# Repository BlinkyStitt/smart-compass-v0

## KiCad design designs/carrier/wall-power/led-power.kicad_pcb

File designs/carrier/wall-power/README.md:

# Wall-power boards

| Board | KiCad layout | KiCad schematic | Finished board |
| --- | --- | --- | --- |
| Internal charger | [Charger PCB](charger.kicad_pcb) | [Charger schematic](charger.kicad_sch) | 24 × 26 mm, 1.60 mm thick |
| Rev A 5 V external pigtail | [Pigtail PCB](usb-pigtail.kicad_pcb) | [Pigtail schematic](usb-pigtail.kicad_sch) | 28 × 31 mm, **1.20 ± 0.10 mm** thick |
| 60 W USB-C inlet | [Inlet PCB](usb-pd60.kicad_pcb) | [Inlet schematic](usb-pd60.kicad_sch) | 28 × 31 mm, **1.20 ± 0.10 mm** thick |
| LED power selector | [Selector PCB](led-power.kicad_pcb) | [Selector schematic](led-power.kicad_sch) | 28 × 28 mm, 1.60 mm thick |

Build the 60 W inlet, selector and existing charger together. Use the
[60 W BOM](bom-pd60.csv) and [assembly guide](../wall-power-pd60.md).
The 5 V pigtail is the earlier option. The 60 W inlet requires the
programmed STUSB4500 profile. Use the keyed connectors in the assembly
guide to preserve the 5 V and return pin order.

Use KiCad 10. Each board has four copper layers. Specify 35 µm finished
outer copper and at least 35 µm on In2.Cu, which carries the power trunks.
Specify 0.13 mm minimum track, 0.20 mm minimum copper clearance and
0.30 mm copper-to-edge clearance. Use plated slots at the USB receptacle
and nonplated locator and mounting holes. Fill and copper-cap the vias
under the soldered exposed pads, and the other vias placed in SMD pads,
to prevent solder loss. The fabrication drill files do not specify
via fill. Tell the assembler which vias are in pads. The selector uses
0.25 mm finished via drills and a 0.50 mm minimum via diameter.

Use the [charger and 5 V pigtail BOM](bom.csv) for those assemblies.
Reflow the boards and solder the wires at the bench. Fit the USB shell
stakes per the assembly house's mixed SMT and through-hole process.
Check capacitor substitutions at DC bias. The charger needs at least
10 µF effective at BAT and SYS. Use the [assembly and bench guide](../wall-power.md)
for wiring, mounting and commissioning.

## Verify or export the boards

From this directory, with KiCad's footprint libraries installed, run the
following for each name in the table. Use a writable output directory.
Use KiCad's Python interpreter for the scripts that import `pcbnew`.

```sh
board=usb-pd60  # or led-power, charger, usb-pigtail
kicad-cli pcb drc --refill-zones --severity-all --exit-code-violations --schematic-parity \
  -o "$output/$board-drc.rpt" "$board.kicad_pcb"
kicad-cli sch export netlist --format kicadxml \
  -o "$output/$board.xml" "$board.kicad_sch"
python verify_netlist.py "$board.kicad_pcb" "$output/$board.xml"
kicad-cli pcb export gerbers --layers F.Cu,In1.Cu,In2.Cu,B.Cu,F.Paste,F.Silkscreen,B.Silkscreen,F.Mask,B.Mask,Edge.Cuts \
  -o "$output/$board/" "$board.kicad_pcb"
kicad-cli pcb export drill --excellon-separate-th -o "$output/$board/" "$board.kicad_pcb"
kicad-cli pcb export pos --format csv --units mm --smd-only \
  -o "$output/$board/placement.csv" "$board.kicad_pcb"
```

The committed PCB files own the final routes. [Board source](board_design.py)
generates the footprints, pin maps and fixed power copper for a new route.
[Schematic source](schematic.py) generates the KiCad connection drawings
from those pin maps. The netlist comparison checks each footprint, reference
and connected pad. The first assembled pair still needs the bench checks.

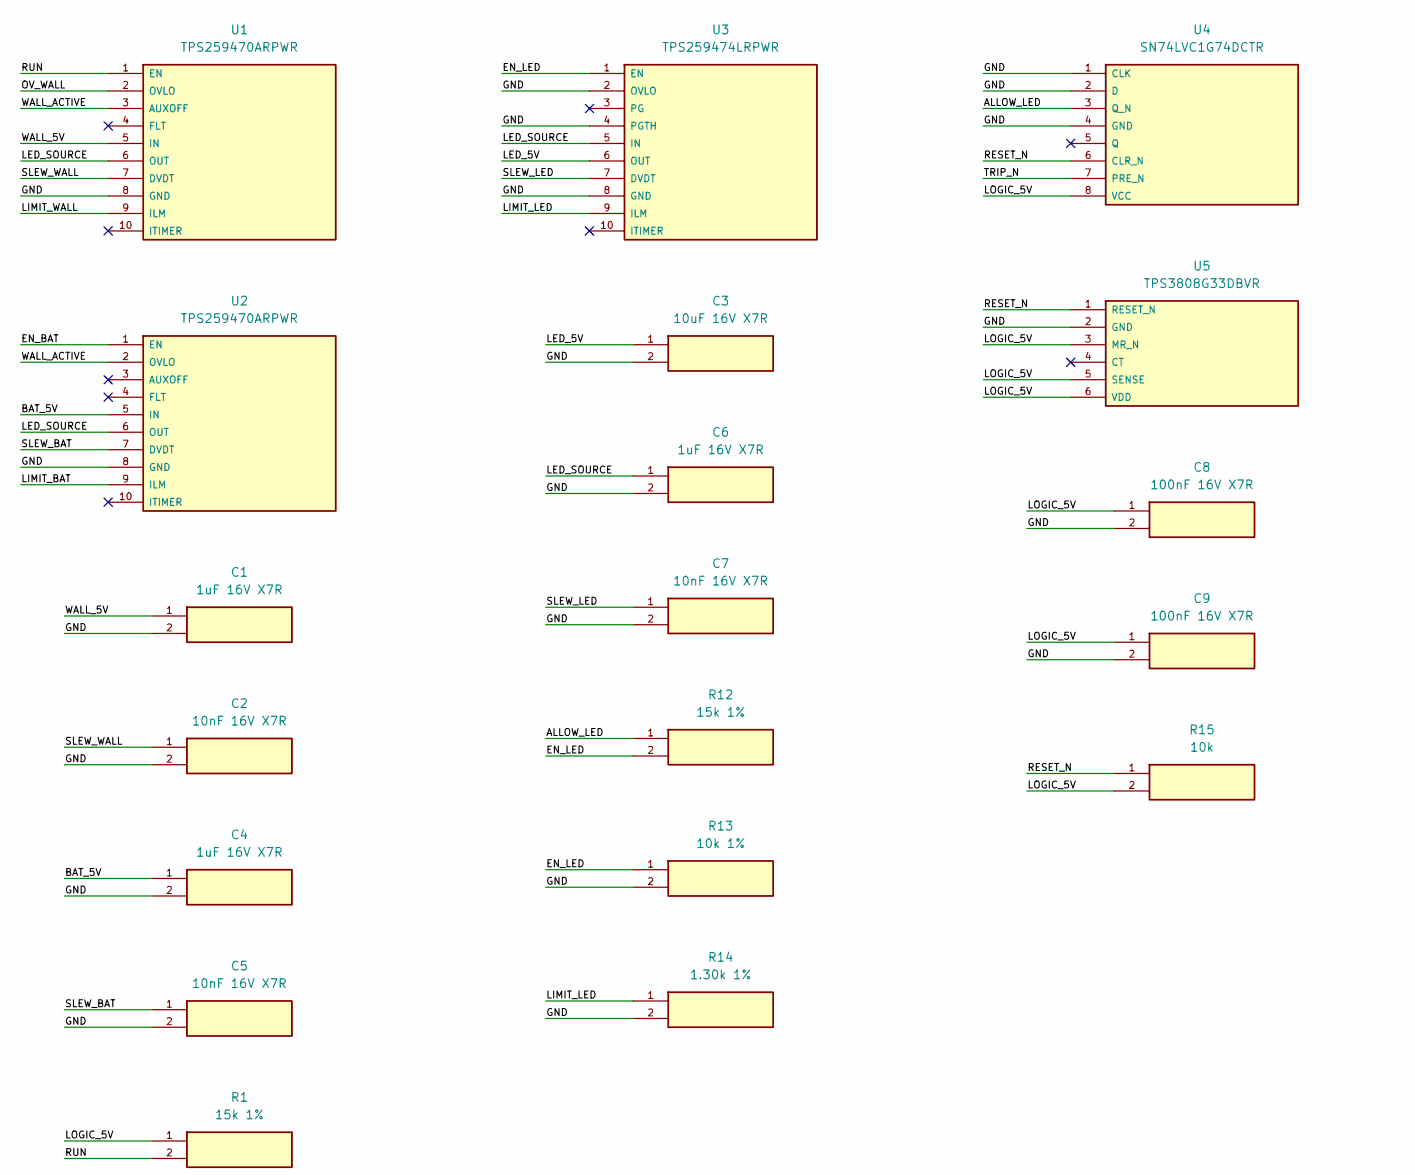
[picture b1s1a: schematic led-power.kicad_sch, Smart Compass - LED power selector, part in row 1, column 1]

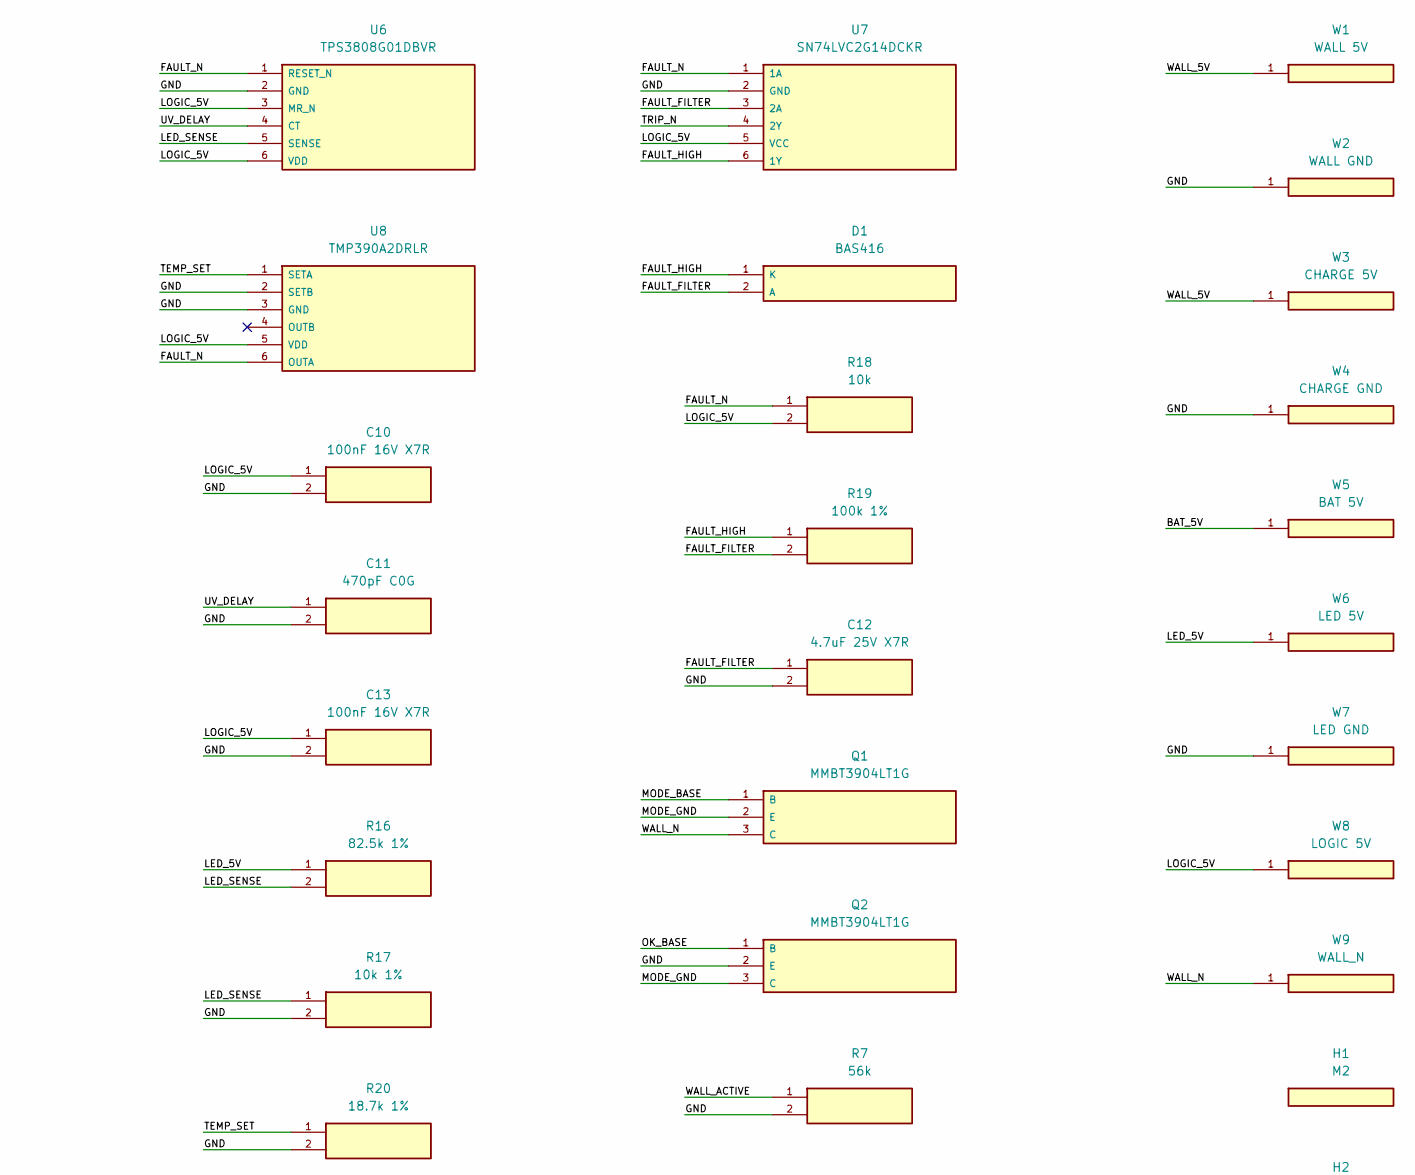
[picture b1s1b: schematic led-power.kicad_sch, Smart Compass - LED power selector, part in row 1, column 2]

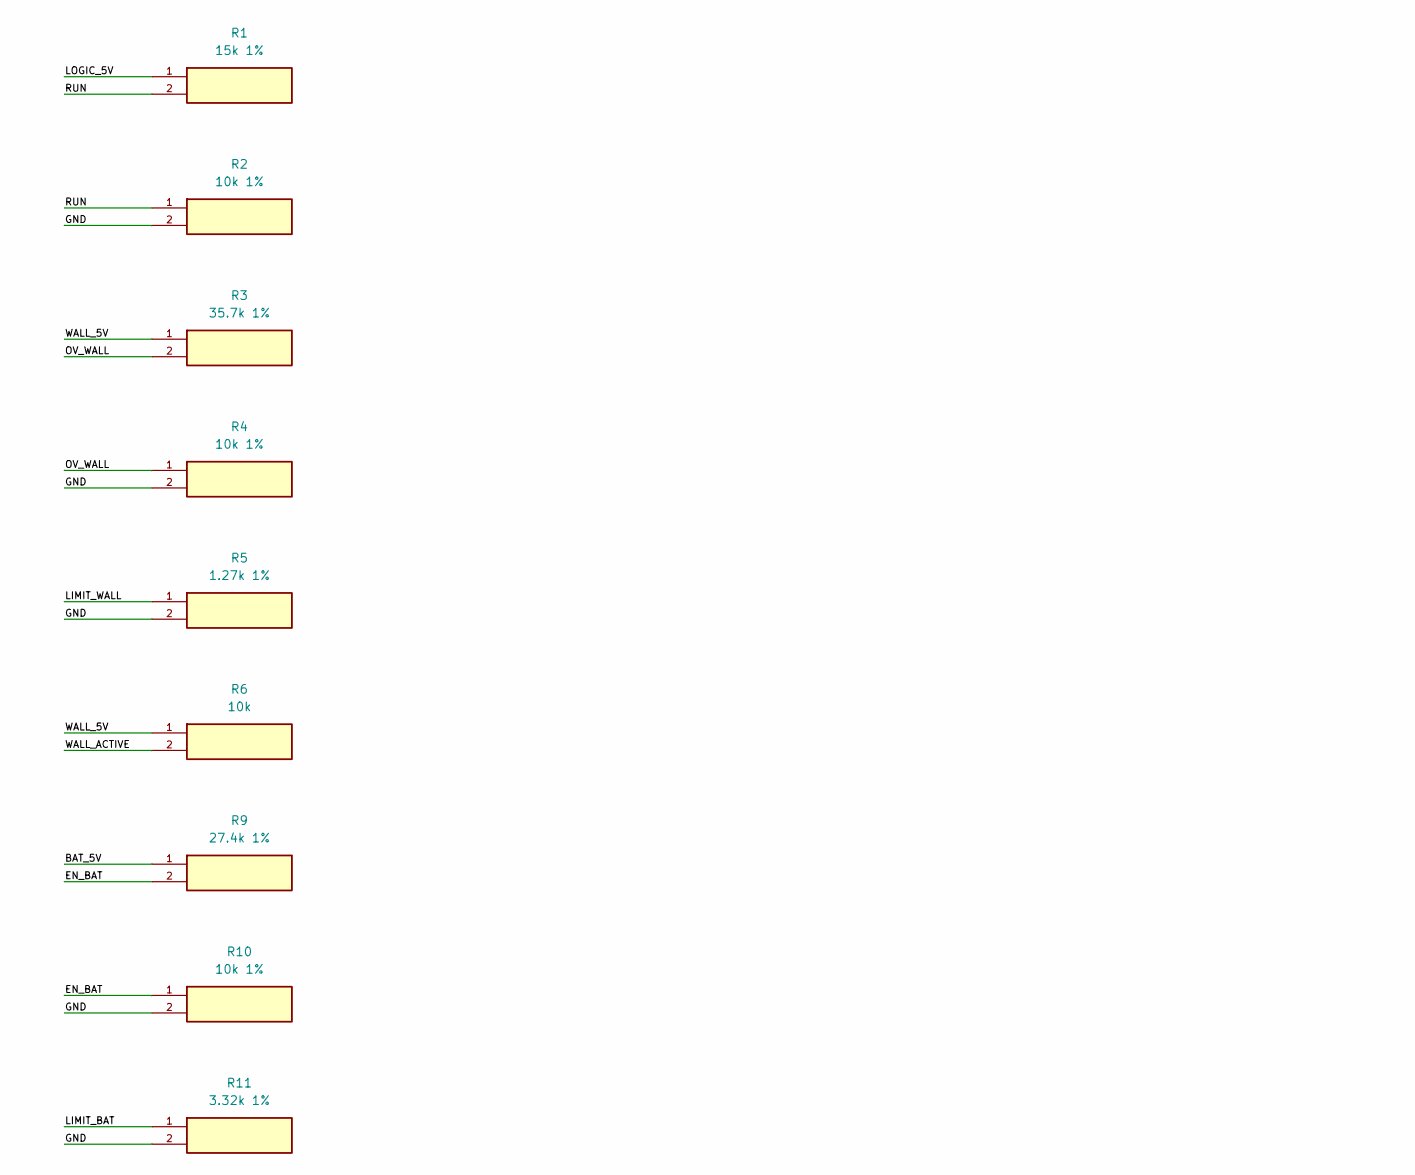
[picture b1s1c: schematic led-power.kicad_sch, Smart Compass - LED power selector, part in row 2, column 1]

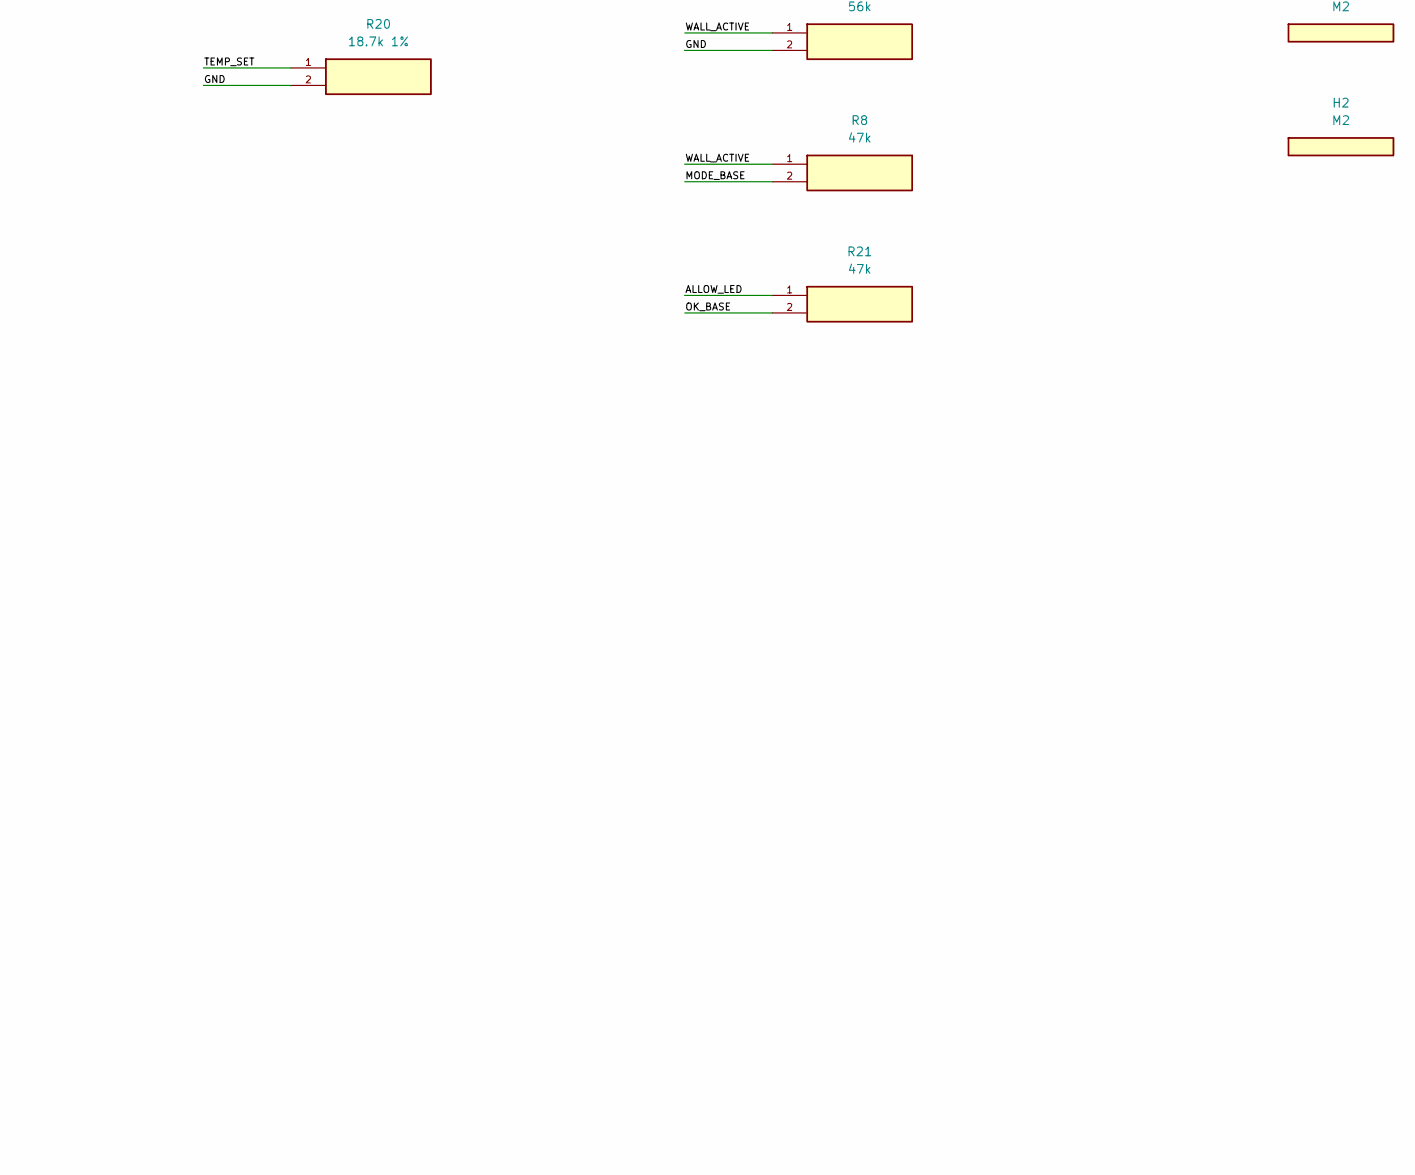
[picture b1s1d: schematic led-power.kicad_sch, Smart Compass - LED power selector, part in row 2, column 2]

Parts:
C1, C4, C6: 1uF 16V X7R; C_0805_2012Metric
C2, C5, C7: 10nF 16V X7R; C_0603_1608Metric
C3: 10uF 16V X7R; C_0805_2012Metric
C8, C9, C10, C13: 100nF 16V X7R; C_0603_1608Metric
C11: 470pF C0G; C_0603_1608Metric
C12: 4.7uF 25V X7R; C_0805_2012Metric
D1: BAS416; D_SOD-323
H1, H2: M2; MountingHole_2.2mm_M2
Q1, Q2: MMBT3904LT1G; SOT-23
R1, R12: 15k 1%; R_0603_1608Metric
R2, R4, R10, R13, R17: 10k 1%; R_0603_1608Metric
R3: 35.7k 1%; R_0603_1608Metric
R5: 1.27k 1%; R_0603_1608Metric
R6, R15, R18: 10k; R_0603_1608Metric
R7: 56k; R_0603_1608Metric
R8, R21: 47k; R_0603_1608Metric
R9: 27.4k 1%; R_0603_1608Metric
R11: 3.32k 1%; R_0603_1608Metric
R14: 1.30k 1%; R_0603_1608Metric
R16: 82.5k 1%; R_0603_1608Metric
R19: 100k 1%; R_0603_1608Metric
R20: 18.7k 1%; R_0603_1608Metric
U1, U2: TPS259470ARPWR; Texas_RPW_VQFN-10_2x2mm
U3: TPS259474LRPWR; Texas_RPW_VQFN-10_2x2mm
U4: SN74LVC1G74DCTR; SSOP-8_2.95x2.8mm_P0.65mm
U5: TPS3808G33DBVR; SOT-23-6
U6: TPS3808G01DBVR; SOT-23-6
U7: SN74LVC2G14DCKR; SOT-363_SC-70-6
U8: TMP390A2DRLR; Texas_DRL0006A_SOT-563
W1: WALL 5V; Lead_18AWG
W2: WALL GND; Lead_18AWG
W3: CHARGE 5V; Lead_22AWG
W4: CHARGE GND; Lead_22AWG
W5: BAT 5V; Lead_22AWG
W6: LED 5V; Lead_22AWG
W7: LED GND; Lead_22AWG
W8: LOGIC 5V; Lead_22AWG
W9: WALL_N; Lead_22AWG

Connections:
/ALLOW_LED: R12.1, R21.1, U4.3 (Q_N)
/BAT_5V: C4.1, R9.1, U2.5 (IN), W5.1
/EN_BAT: R9.2, R10.1, U2.1 (EN)
/EN_LED: R12.2, R13.1, U3.1 (EN)
/FAULT_FILTER: C12.1, D1.2 (A), R19.2, U7.3 (2A)
/FAULT_HIGH: D1.1 (K), R19.1, U7.6 (1Y)
/FAULT_N: R18.1, U6.1 (RESET_N), U7.1 (1A), U8.6 (OUTA)
/GND: C1.2, C2.2, C3.2, C4.2, C5.2, C6.2, C7.2, C8.2, C9.2, C10.2, C11.2, C12.2, C13.2, Q2.2 (E), R2.2, R4.2, R5.2, R7.2, R10.2, R11.2, R13.2, R14.2, R17.2, R20.2, U1.8 (GND), U2.8 (GND), U3.2 (OVLO), U3.4 (PGTH), U3.8 (GND), U4.1 (CLK), U4.2 (D), U4.4 (GND), U5.2 (GND), U6.2 (GND), U7.2 (GND), U8.2 (SETB), U8.3 (GND), W2.1, W4.1, W7.1
/LED_5V: C3.1, R16.1, U3.6 (OUT), W6.1
/LED_SENSE: R16.2, R17.1, U6.5 (SENSE)
/LED_SOURCE: C6.1, U1.6 (OUT), U2.6 (OUT), U3.5 (IN)
/LIMIT_BAT: R11.1, U2.9 (ILM)
/LIMIT_LED: R14.1, U3.9 (ILM)
/LIMIT_WALL: R5.1, U1.9 (ILM)
/LOGIC_5V: C8.1, C9.1, C10.1, C13.1, R1.1, R15.2, R18.2, U4.8 (VCC), U5.3 (MR_N), U5.5 (SENSE), U5.6 (VDD), U6.3 (MR_N), U6.6 (VDD), U7.5 (VCC), U8.5 (VDD), W8.1
/MODE_BASE: Q1.1 (B), R8.2
/MODE_GND: Q1.2 (E), Q2.3 (C)
/OK_BASE: Q2.1 (B), R21.2
/OV_WALL: R3.2, R4.1, U1.2 (OVLO)
/RESET_N: R15.1, U4.6 (CLR_N), U5.1 (RESET_N)
/RUN: R1.2, R2.1, U1.1 (EN)
/SLEW_BAT: C5.1, U2.7 (DVDT)
/SLEW_LED: C7.1, U3.7 (DVDT)
/SLEW_WALL: C2.1, U1.7 (DVDT)
/TEMP_SET: R20.1, U8.1 (SETA)
/TRIP_N: U4.7 (PRE_N), U7.4 (2Y)
/UV_DELAY: C11.1, U6.4 (CT)
/WALL_5V: C1.1, R3.1, R6.1, U1.5 (IN), W1.1, W3.1
/WALL_ACTIVE: R6.2, R7.1, R8.1, U1.3 (AUXOFF), U2.2 (OVLO)
/WALL_N: Q1.3 (C), W9.1

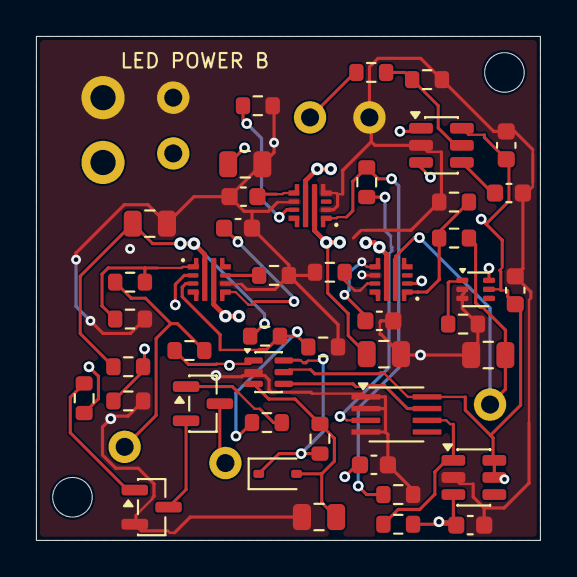
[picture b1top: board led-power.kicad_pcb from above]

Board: 4 copper layers, 28.0 x 28.0 mm, 56 parts (0 on the bottom side), 30 nets.

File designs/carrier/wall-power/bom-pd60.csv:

assembly,reference,part,description
usb-pd60,J1,USB4736-GF-A-KIT,Receptacle and USBTJ-06 gasket
usb-pd60,U1,STUSB4500QTR,Program 5 V and 20 V 3 A profiles
usb-pd60,U2,TPS259470ARPWR,Contract and input eFuse
usb-pd60,U3,TPS259470LRPWR,5 V output eFuse
usb-pd60,D1,ESDA25W,CC line protection
usb-pd60,D2,ESDA25P35-1U1M,VBUS protection
usb-pd60,C1,4.7uF 50V X7R,1206
usb-pd60,C2 C3,1uF 16V X7R,0603
usb-pd60,C4 C6,1uF 50V X7R,0805
usb-pd60,C5,10nF 50V X7R,0603
usb-pd60,C8,10nF 16V X7R,0603
usb-pd60,C7,10uF 16V X7R,0805
usb-pd60,R1 R2,1k,0603
usb-pd60,R3,100k 1%,0603
usb-pd60,R4,22k 1%,0603
usb-pd60,R5,140k 1%,0603
usb-pd60,R6 R9 R11,10k 1%,0603
usb-pd60,R7,1.24k 1%,0603
usb-pd60,R8,27.4k 1%,0603
usb-pd60,R10,35.7k 1%,0603
usb-pd60,R12,549R 1%,0603
usb-pd60,R13 R14,4.7k,0603
usb-pd60,R15,100k,0603
led-power,U1 U2,TPS259470ARPWR,Reverse-blocking power switches
led-power,U3,TPS259474LRPWR,Shared latch-off LED circuit breaker
led-power,U4,SN74LVC1G74DCTR,Logic-powered LED fault latch
led-power,U5,TPS3808G33DBVR,Power-on reset
led-power,U6,TPS3808G01DBVR,LED output undervoltage sensor
led-power,U7,SN74LVC2G14DCKR,Schmitt filter for sustained faults
led-power,U8,TMP390A2DRLR,Selector temperature switch
led-power,D1,BAS416,Fast fault timer discharge
led-power,Q1 Q2,MMBT3904LT1G,Open-collector status for GPIO18
led-power,C1 C4 C6,1uF 16V X7R,0805
led-power,C2 C5 C7,10nF 16V X7R,0603
led-power,C3,10uF 16V X7R,0805
led-power,C8 C9 C10 C13,100nF 16V X7R,0603
led-power,C11,470pF C0G,0603
led-power,C12,4.7uF 25V X7R,0805 with 3.3 to 5.7uF effective over voltage and temperature
led-power,R1 R12,15k 1%,0603
led-power,R2 R4 R10 R13 R17,10k 1%,0603
led-power,R3,35.7k 1%,0603
led-power,R5,1.27k 1%,0603
led-power,R6 R15 R18,10k,0603
led-power,R7,56k,0603
led-power,R8 R21,47k,0603
led-power,R9,27.4k 1%,0603
led-power,R11,3.32k 1%,0603
led-power,R14,1.30k 1%,0603
led-power,R16,82.5k 1%,0603
led-power,R19,100k 1%,0603
led-power,R20,18.7k 1%,0603
inlet,converter,D24V90F5,Pololu 2866
inlet,mounts,M2 screws and insulating washers,Two inlet mounts and four regulator mounts
inlet,cap,USB-C dust cap,Tethered cap for charging inlet
harness,5 V feed,18 AWG pair,Internal inlet to selector
harness,inlet receptacle,39012020,Molex Mini-Fit Jr. two-position receptacle
harness,selector plug,39012021,Molex Mini-Fit Jr. two-position plug
harness,inlet female contacts,39000039,Mini-Fit Jr. 18 AWG receptacle terminal
harness,selector male contacts,39000041,Mini-Fit Jr. 18 AWG plug terminal

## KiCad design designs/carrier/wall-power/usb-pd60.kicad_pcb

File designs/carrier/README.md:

# Plug-in carrier for the narrow compass

Rev A has a [routed carrier PCB](carrier-a.kicad_pcb), a
[plug and harness assembly guide](assembly.md), and a
[60 W USB-C wall power and charging](wall-power-pd60.md). The charger is a separate
assembly that plugs into the carrier. The [sealed USB-C inlet](dust-sealing.md) faces down
from a pocket in the rear cover. The inlet board and 5 V regulator fit inside
that pocket. The complete enclosure seals and temperatures still need
physical verification.

The original fit model uses a single 1.2 mm carrier board. The
housing uses the narrow design's 58.1 mm optical stack and removable protected
cell. The board follows the cavity and sits beside the battery bay. Its seven
mounts are part of the ribbed rear cover. The rear cover also has holes for
three panel-mount buttons. The layout budgets 36 off-board conductors,
compared with 92 in the current fixed loom. The print set has 12 parts.
One removable retainer holds all seven boards on the rear cover. The
gasketed battery hatch uses four screws and keeps the independent cell keeper.
The cradle includes both fixed contact seats. Each cell end has one removable
insulating clamp. The rear cover includes the disconnect guard.

Three Keystone 3153 insulating washers take the place of the printed
Fibonacci clips. The fit check includes movement around the screw shaft and
checks bearing and clearance to the LEDs and optics. Check clamping and
retention on the physical assembly. [Keystone catalog](https://beta.keyelco.com/userAssets/file/M70p144.pdf)

## Module interfaces

- The GPS FeatherWing, classic LSM9DS1, RFM95W, and BlackPill use complete
  low-profile header strips. The terminal schedule records each pin, its source
  pad, its nominal position, and its circuit assignment. Leave unassigned pins
  unconnected. The module-side male headers need one bench soldering operation.
- The Sparkle Motion uses a 2 × 3 header at JP3. Keep the original barrel
  jack and screw-terminal block. Use a center-positive power lead and a
  five-conductor lead for the LED terminal group. The CAD reserves space for
  each exit. Check the exact connectors and bend radii before routing.
- The PowerBoost has space for removable power leads. The original R20.2
  connection is shown in the terminal schedule only to identify the behavior
  that the new circuit must replace. The carrier needs a circuit that preserves
  physical disconnect and low-battery shutdown through stock module interfaces.

The socket reference is the [Mill-Max 315/415 and 335/435 mated stack](https://www.mill-max.com/sites/default/files/external/assets/2018-03/PR685%20-%20Super%20Low%20Profile%20sockets%20315%20-%20415.pdf).
The drawings give 3.94 mm between the boards. Check supplied hole sizes,
soldered pin insertion, and module retention on the physical gauge.

## Harness slack and assembly

The fit report lists the installed slack allowance for each of the 13 off-board
cables. Allow 20–25 mm on local leads and 40 mm on the four LED cables that cross
to the front. These lengths stay in the finished harness. Measure the route
between the actual connector exits with its ordinary bends, then add the
service allowance and the wire inside each connector. Make the first cables
against the fitted hardware before setting the final cut list.

Lift the rear cover straight back and support it about 30 mm off the case. The LED leads
have a further 10 mm of handling allowance to reach their plugs. Unplug those
leads before taking the cover away. Keep some play at each connector and
support the lead near its exit. Lay the excess into the blue service-fold
spaces in the CAD as separate flat U-bends. Keep the wires free to slide against
each other through the turn and use a removable soft tie to keep each fold in
its space. Keep the door, cover rim, screw seats, and LED board clear.

The slots use the largest specified individual wire diameter for each cable
and at least three times that diameter for the wire centreline bend radius. Use the
larger bend radius if the selected cable or connector requires one. Check the
actual lead exits and the opened and closed assembly with the first set of
cables. [Wire support and bend-radius reference](https://standards.nasa.gov/sites/default/files/standards/NASA/A/4/nasa-std-87394a_w_change_4_0.pdf)

## Make the Rev A print package

From the repository root, choose a new fit folder and a new package folder on
the external drive. Set `CARRIER_FIT` and `CARRIER_PRINTS` to their absolute
paths. Fetch the native assets with Git LFS. Run the routed fit macro in
FreeCAD, then run the package builder with
PrusaSlicer installed. Wait for `REV A BATTERY MOTION PASS` in the FreeCAD
console and check for `routed-fit.json` before packaging.

```sh
mkdir "$CARRIER_FIT"
COMPASS_CARRIER_SOURCE="$PWD/designs/carrier" \
COMPASS_CARRIER_OUTPUT="$CARRIER_FIT" \
/Applications/FreeCAD.app/Contents/Resources/bin/freecad "$PWD/designs/carrier/RunRoutedFit.FCMacro"

python3 designs/carrier/print_package.py "$CARRIER_FIT" "$CARRIER_PRINTS"
```

The builder checks and slices the 12 installed parts. It uses the revised
rear cover, shell, front bezel, cradle, hatch, keeper and retainer from the routed fit.
It uses the matching narrow exports for the other parts. Read the [printing and first-fit guide](printing.md)
before printing.

Use `Run.FCMacro` for the socket drill gauge and legacy fit reference. It
writes the gauge, assembly, terminal schedule and unrouted placement board.

## Automated checks

The Carrier power checks workflow runs the firmware tests, KiCad checks,
and the complete fit and print build. Download the reports and reference
print projects from the workflow run. To run the board checks locally,
use KiCad 10, its footprint libraries, and an interpreter with `pcbnew`.

```sh
bash designs/carrier/check_boards.sh "$CARRIER_REPORTS"
```

Set `KICAD_CLI` and `KICAD_PYTHON` if those commands are installed outside
your normal search path.

## Qualify the prototype

Use the Rev A assembly and power guides for the bench build. Measure current
and temperature at the contacts, copper, and LED circuits. Check the GPS
and radio antennas with the carrier installed. Check the retainer pads,
APEM buttons, seals and lead exits on the
printed cover. Use the routed charger, 60 W inlet and LED selector boards. The
[60 W guide](wall-power-pd60.md) covers their keyed harnesses.

The report compares the old loom, removed prints, new rear cover, laminate and
copper budget. The remaining allowance must cover sockets, replacement leads,
new retention and panel hardware, and any changes to the power circuit. The
finished assembly must be weighed.

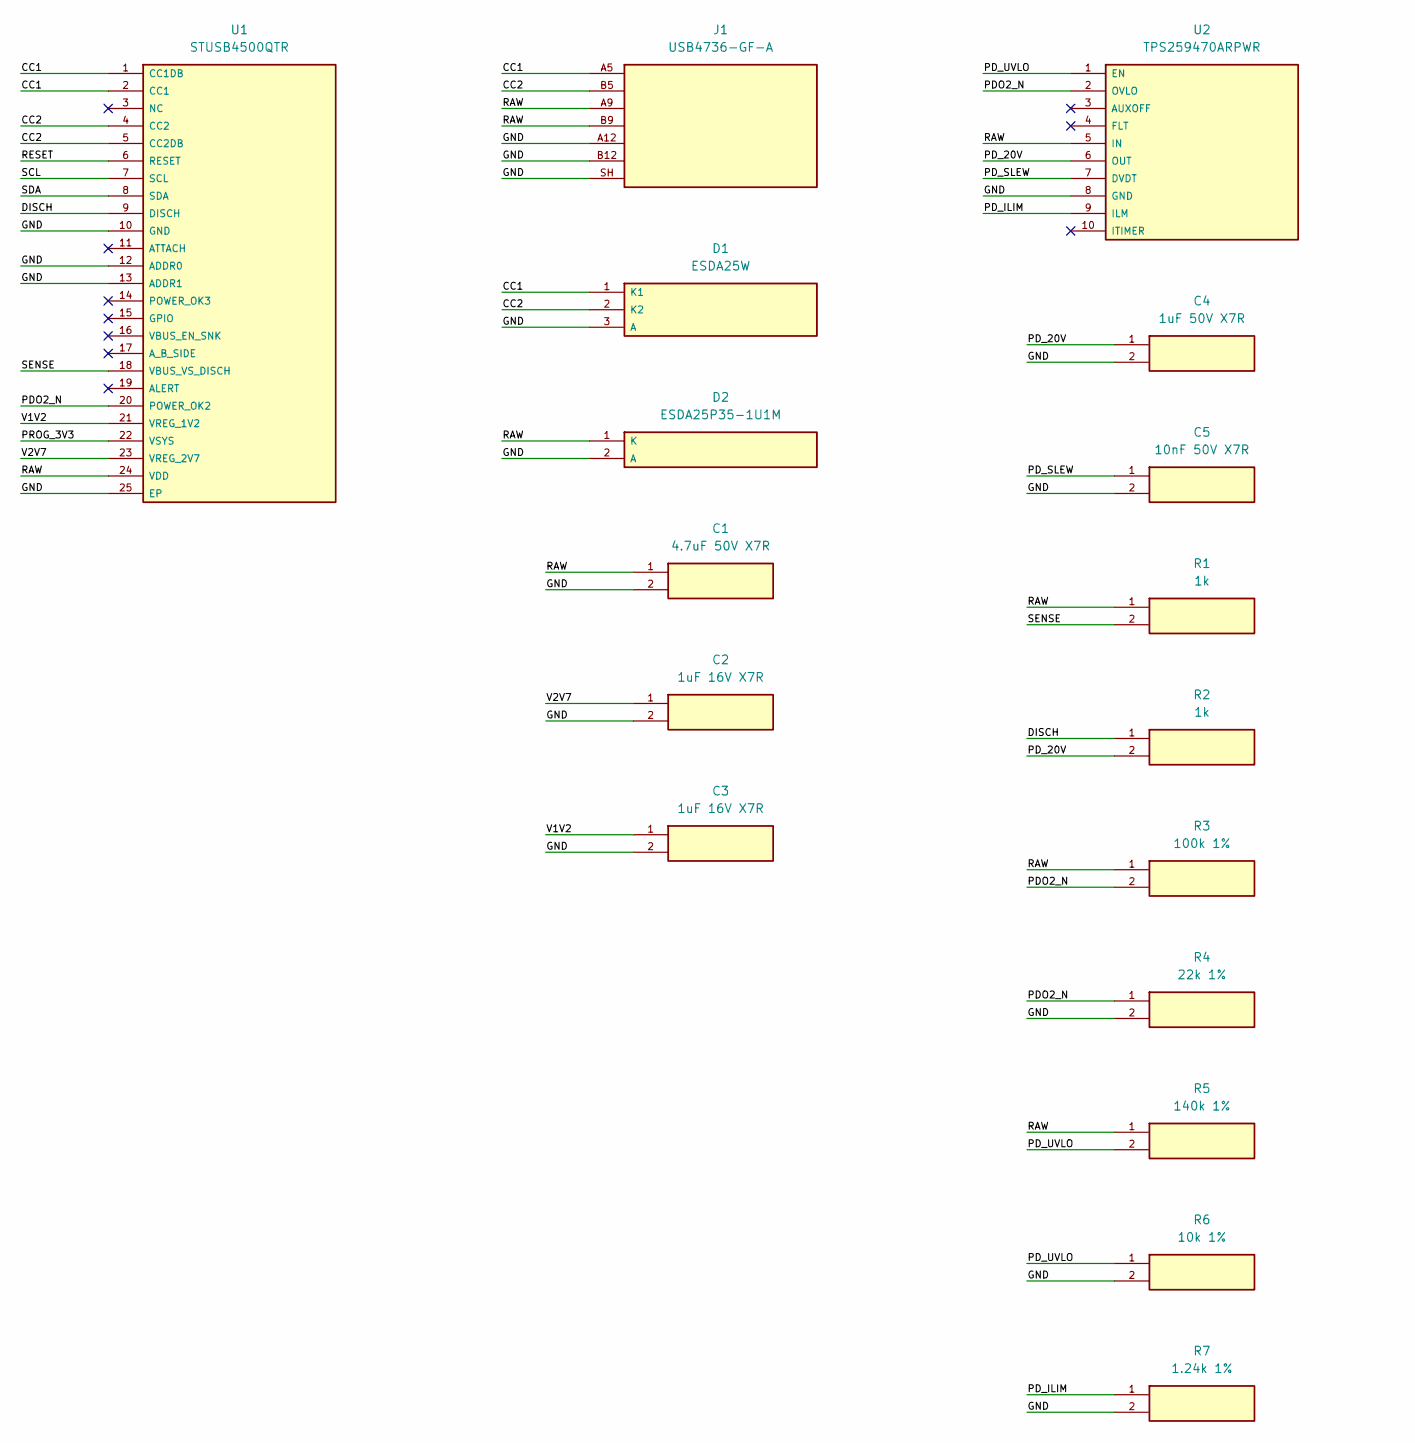
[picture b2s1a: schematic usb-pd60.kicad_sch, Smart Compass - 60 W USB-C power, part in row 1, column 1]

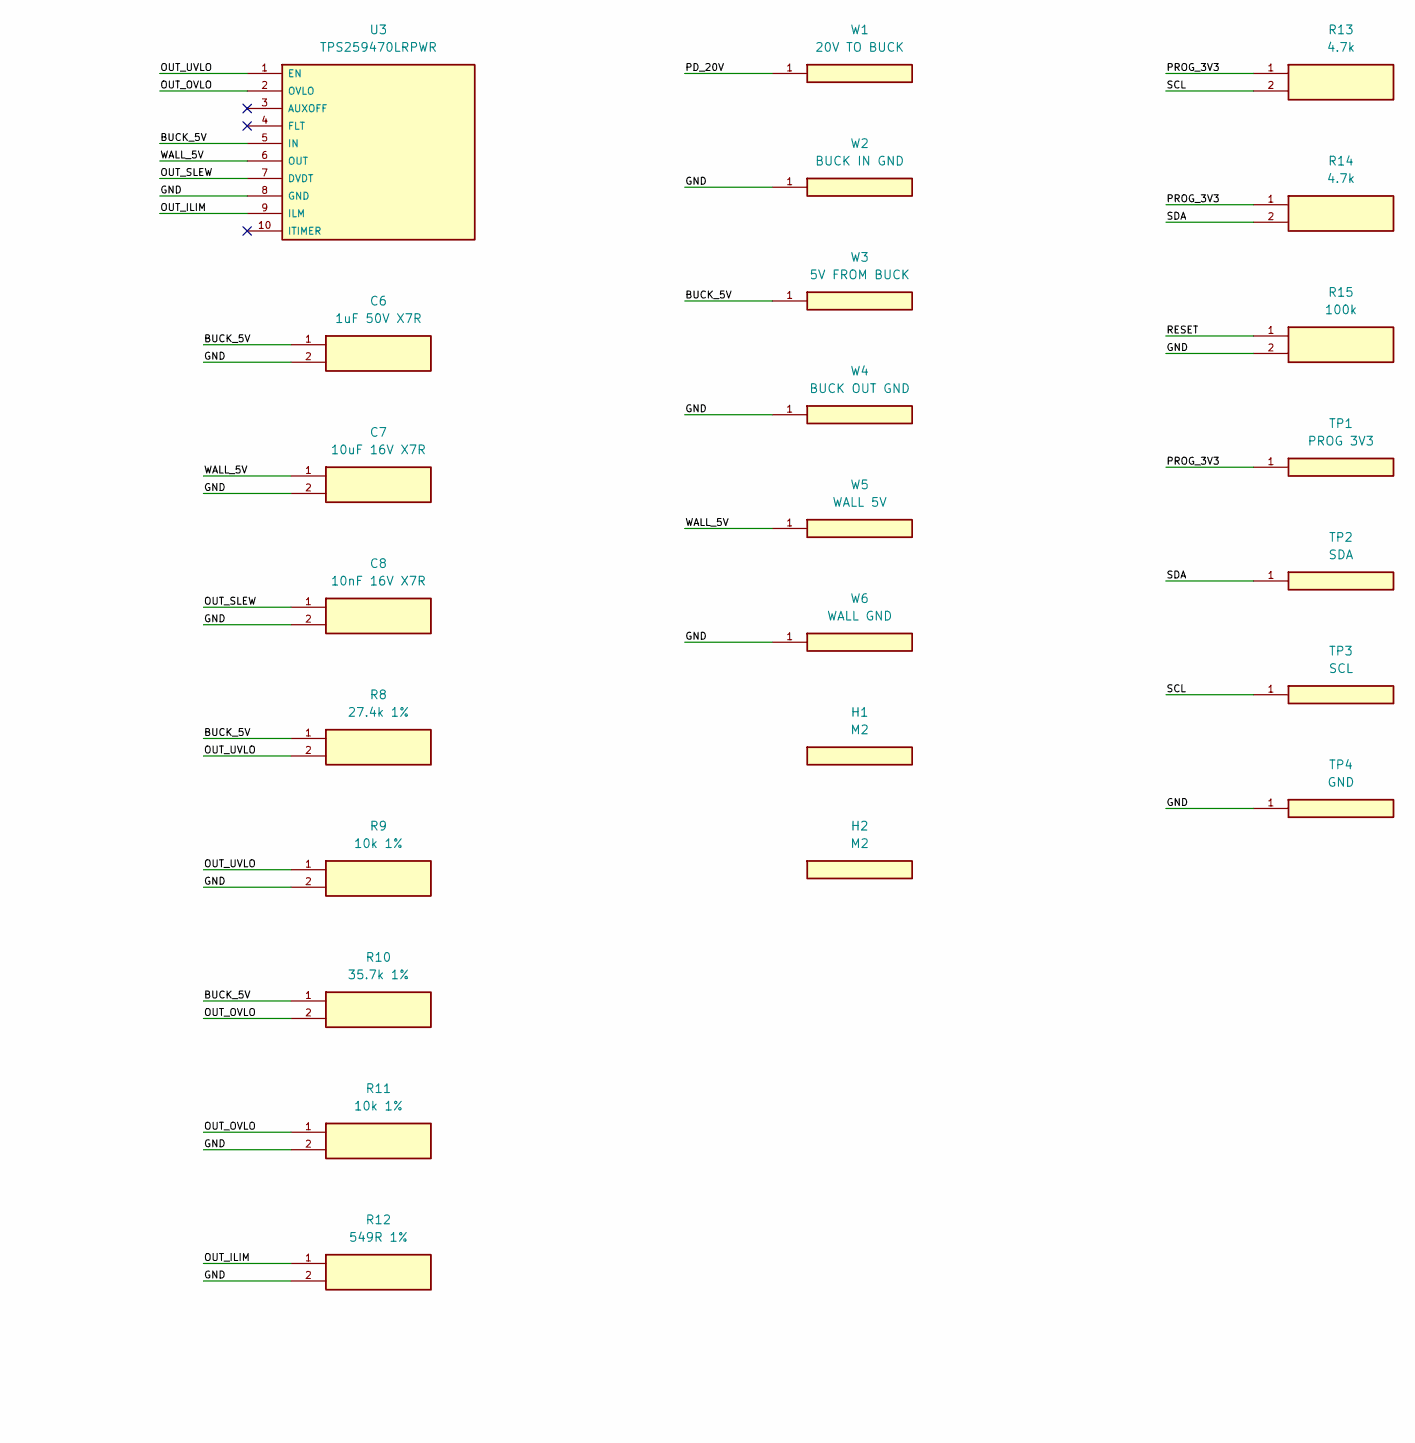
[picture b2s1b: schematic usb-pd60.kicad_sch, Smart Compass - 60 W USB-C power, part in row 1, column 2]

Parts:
C1: 4.7uF 50V X7R; C_1206_3216Metric
C2, C3: 1uF 16V X7R; C_0603_1608Metric
C4, C6: 1uF 50V X7R; C_0805_2012Metric
C5: 10nF 50V X7R; C_0603_1608Metric
C7: 10uF 16V X7R; C_0805_2012Metric
C8: 10nF 16V X7R; C_0603_1608Metric
D1: ESDA25W; SOT-323_SC-70
D2: ESDA25P35-1U1M; ST_QFN-2L_1.6x1mm
H1, H2: M2; MountingHole_2.2mm_M2
J1: USB4736-GF-A
R1, R2: 1k; R_0603_1608Metric
R3: 100k 1%; R_0603_1608Metric
R4: 22k 1%; R_0603_1608Metric
R5: 140k 1%; R_0603_1608Metric
R6, R9, R11: 10k 1%; R_0603_1608Metric
R7: 1.24k 1%; R_0603_1608Metric
R8: 27.4k 1%; R_0603_1608Metric
R10: 35.7k 1%; R_0603_1608Metric
R12: 549R 1%; R_0603_1608Metric
R13, R14: 4.7k; R_0603_1608Metric
R15: 100k; R_0603_1608Metric
TP1: PROG 3V3; TestPoint_Pad_D1.0mm
TP2: SDA; TestPoint_Pad_D1.0mm
TP3: SCL; TestPoint_Pad_D1.0mm
TP4: GND; TestPoint_Pad_D1.0mm
U1: STUSB4500QTR; QFN-24-1EP_4x4mm_P0.5mm_EP2.7x2.7mm
U2: TPS259470ARPWR; Texas_RPW_VQFN-10_2x2mm
U3: TPS259470LRPWR; Texas_RPW_VQFN-10_2x2mm
W1: 20V TO BUCK; Lead_22AWG
W2: BUCK IN GND; Lead_22AWG
W3: 5V FROM BUCK; Lead_18AWG
W4: BUCK OUT GND; Lead_18AWG
W5: WALL 5V; Lead_18AWG
W6: WALL GND; Lead_18AWG

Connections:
/BUCK_5V: C6.1, R8.1, R10.1, U3.5 (IN), W3.1
/CC1: D1.1 (K1), J1.A5, U1.1 (CC1DB), U1.2 (CC1)
/CC2: D1.2 (K2), J1.B5, U1.4 (CC2), U1.5 (CC2DB)
/DISCH: R2.1, U1.9 (DISCH)
/GND: C1.2, C2.2, C3.2, C4.2, C5.2, C6.2, C7.2, C8.2, D1.3 (A), D2.2 (A), J1.A12, J1.B12, J1.SH, R4.2, R6.2, R7.2, R9.2, R11.2, R12.2, R15.2, TP4.1, U1.10 (GND), U1.12 (ADDR0), U1.13 (ADDR1), U1.25 (EP), U2.8 (GND), U3.8 (GND), W2.1, W4.1, W6.1
/OUT_ILIM: R12.1, U3.9 (ILM)
/OUT_OVLO: R10.2, R11.1, U3.2 (OVLO)
/OUT_SLEW: C8.1, U3.7 (DVDT)
/OUT_UVLO: R8.2, R9.1, U3.1 (EN)
/PDO2_N: R3.2, R4.1, U1.20 (POWER_OK2), U2.2 (OVLO)
/PD_20V: C4.1, R2.2, U2.6 (OUT), W1.1
/PD_ILIM: R7.1, U2.9 (ILM)
/PD_SLEW: C5.1, U2.7 (DVDT)
/PD_UVLO: R5.2, R6.1, U2.1 (EN)
/PROG_3V3: R13.1, R14.1, TP1.1, U1.22 (VSYS)
/RAW: C1.1, D2.1 (K), J1.A9, J1.B9, R1.1, R3.1, R5.1, U1.24 (VDD), U2.5 (IN)
/RESET: R15.1, U1.6 (RESET)
/SCL: R13.2, TP3.1, U1.7 (SCL)
/SDA: R14.2, TP2.1, U1.8 (SDA)
/SENSE: R1.2, U1.18 (VBUS_VS_DISCH)
/V1V2: C3.1, U1.21 (VREG_1V2)
/V2V7: C2.1, U1.23 (VREG_2V7)
/WALL_5V: C7.1, U3.6 (OUT), W5.1

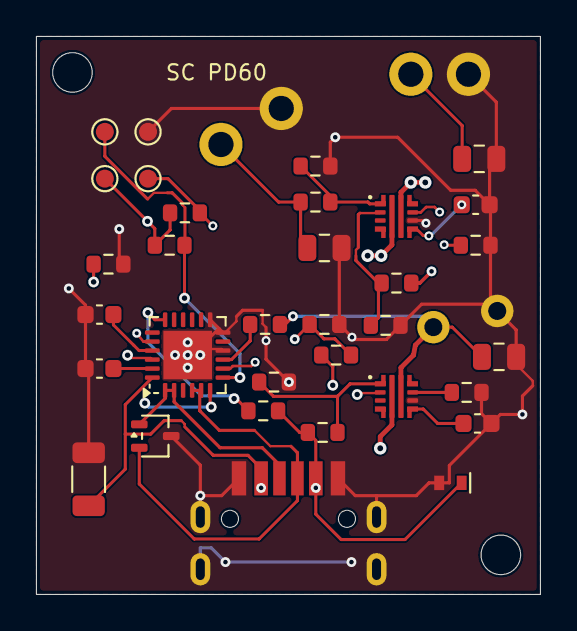
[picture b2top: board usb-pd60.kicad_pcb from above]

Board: 4 copper layers, 28.0 x 31.0 mm, 41 parts (0 on the bottom side), 23 nets.
